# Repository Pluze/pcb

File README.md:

# PCB

Reference and experimental PCB designs built with KiCad, plus reusable agent workflows for schematic capture, placement, routing, and verification.

## Contents

- [`Designs/LM555_LED_Flasher`](Designs/LM555_LED_Flasher): an all-SMT, single-sided 555 timer LED flasher adapted from a classroom reference.
- [`Designs/Ionto_Current_Source_Core`](Designs/Ionto_Current_Source_Core): a single-channel R1218 constant-current boost prototype.
- [`Designs/Electrode_Snap_Adapter_Series`](Designs/Electrode_Snap_Adapter_Series): four circular-contact adapters and a 17-up U4 panel.
- [`tools/pcbflow`](tools/pcbflow): public CLI, reusable engines and tests for humans and agents.
- [`.agents/skills`](.agents/skills): engineering methods and shared design defaults.

## Design Philosophy

Design intent is made explicit before editing. Schematic connectivity, footprints, placement, routing, silkscreen, and final renders are validated as separate gates. Classroom and prototype boards favor readable documentation, common packages, generous geometry, and reproducible evidence.

The workflows draw on KiCad's official IPC model and public agent-oriented KiCad projects, while keeping tool-specific claims tied to verified local behavior. See each design's `VALIDATION.md` for measured results and remaining warnings.

Use `./pcb finish --design NAME` to complete a saved design through clean autorouting,
review, adoption, copper pour and production build. Use `./pcb build` to refresh U4,
LightBurn and complete supplier Gerber packages together. `./pcb verify` checks the
current delivery. Add `--json` before the command for agent-readable results.

The [tool guide](tools/pcbflow/README.md) covers human/agent handoffs, staged commands,
advanced tools, output ownership and verification commands.

## Status

These projects are educational references and experiments. They are not production-certified hardware. Verify component data, electrical limits, PCB fabrication rules, assembly requirements, and safety constraints before manufacturing or use.

## Contributing

Read [`AGENTS.md`](AGENTS.md), [`Designs/AGENTS.md`](Designs/AGENTS.md), and [`CONTRIBUTING.md`](CONTRIBUTING.md) before changing a design.

## License

MIT. See [`LICENSE`](LICENSE).

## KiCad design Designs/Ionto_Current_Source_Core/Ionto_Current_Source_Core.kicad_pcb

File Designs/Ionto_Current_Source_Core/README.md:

# R1218N041A Single-Channel Constant-Current Core

This project is a minimum verifiable implementation of the paper's R1218-based stimulation architecture. It accepts a protected 1-cell LiPo and provides one two-wire constant-current output. Charging, timing, wireless power, channel decoding, switches, and miniaturization are deliberately omitted.

This is an experimental electrical prototype, not a medically certified device. Do not connect it to a person until current limits, isolation, electrodes, open-load behavior, fault behavior, and applicable safety requirements have been reviewed by a qualified engineer.

## Electrical operation

`U1` is `R1218N041A-TR-FE`, a SOT-23-6 boost LED/current driver with an internal switch, internal rectifier diode, 0.2 V feedback reference, and approximately 18.5 V typical over-voltage protection. `CE` is routed to J3 instead of being permanently tied high.

J3 is a two-pin 2.54 mm SMT header:

- Pin 1: VIN / always-on source
- Pin 2: CE / external enable input

Fit a standard 2.54 mm shunt across pins 1–2 for always-on operation. Remove the shunt and drive pin 2 for external control. The external controller must share board GND through a separate ground connection.

The R1218 includes a CE pull-down specified at 600 kΩ to 2.2 MΩ, so removing the shunt leaves the converter disabled even when no external controller is attached. For an external logic source, the datasheet specifies CE low at no more than 0.5 V and CE high at at least 1.5 V; the CE pin must remain within its absolute input limits relative to the battery/GND domain.

The current path is:

`VBAT → L1 → U1 internal boost stage → VOUT → J2 pin 1 → external load → J2 pin 2 → VFB → R1 → GND`

U1 regulates the VFB node to nominally 0.2 V, so:

`ISTIM = 0.2 V / R1`

The default `R1 = 536 Ω ±1%` gives `ISTIM ≈ 373 µA`, corresponding to approximately 0.261 mA/cm² over 143 mm². For the 199 mm² electrode, use the 402 Ω carrier for approximately 498 µA or 0.250 mA/cm². The R1218 feedback specification is 0.19–0.21 V, so IC feedback tolerance alone produces approximately ±5% current variation before resistor tolerance and operating effects.

## Assembly-selected current

| R1 | Nominal current | Use |
|---:|---:|---|
| 665 Ω | 301 µA | Low end of configured range |
| 536 Ω | 373 µA | 143 mm² default |
| 402 Ω | 498 µA | 199 mm² default |
| 267 Ω | 749 µA | Intermediate setting |
| 200 Ω | 1.00 mA | Larger-area validation setting |
| 133 Ω | 1.50 mA | Nominal maximum setting |

For a fixed-current carrier, use one fixed resistor per assembly. The main board carries a two-position 2.54 mm SMT female socket. R1 is mounted on a removable two-pin RSET carrier made from a mating `TSM-102-01-S-SV` header and a tiny carrier PCB; it is not inserted into the socket as a bare 0805 part. This keeps resistor changes solder-free at the core board. Do not populate multiple fixed values in parallel.

For bench adjustment, a Bourns `3223W-1-102E` 1 kΩ, 11-turn, top-adjust SMD trimmer can replace the fixed RSET electrically. Connect it as a two-terminal rheostat by tying the wiper to one end, then connect those two effective terminals to the two existing RSET pads. Its physical three-pad footprint does not match the present two-pad RSET socket, so use short wires or a simple two-pin header connection for validation rather than soldering it directly onto the socket footprint. Approximately 667 Ω sets 300 µA, 402 Ω sets 498 µA, 267 Ω sets 749 µA, 200 Ω sets 1.00 mA, and 133 Ω sets 1.50 mA. Preset the resistance with a meter before power-up; the trimmer scale is not a calibrated current indication.

## Component roles and selected parts

| Ref | Selected part/value | Package/footprint | Purpose |
|---|---|---|---|
| J1 | Samtec `TSM-102-01-S-SV` | 1×2, 2.54 mm vertical SMT header | Protected 1S LiPo input; pin 1 BAT+, pin 2 GND; accepts a simple flying-lead harness |
| U1 | Nisshinbo `R1218N041A-TR-FE` | SOT-23-6 | Boost conversion and 0.2 V constant-current regulation |
| L1 | Bourns `SRN4018-220M`, 22 µH | 4.0 × 4.0 mm SMD | Boost energy storage; 900 mA rated, shielded |
| C1 | Murata `GRM21BR71A105KA01L`, 1 µF 10 V X7R | 0805 hand-solder pads | Battery/input bypass |
| C2 | KEMET `C0805C224K5RACTU`, 0.22 µF 50 V X7R | 0805 hand-solder pads | Boost/output filtering |
| R1 | Yageo `RC0805FR-07536RL`, 536 Ω 1% | 0805 on removable two-pin RSET carrier | Default 373 µA setting for 143 mm² electrode |
| RT1 option | Bourns `3223W-1-102E`, 1 kΩ ±20%, 11-turn | 3.9 × 3.2 mm top-adjust SMD trimmer connected to the two RSET pads | Adjustable validation replacement for the fixed RSET |
| XS1 | Samtec `SSM-102-L-SV-K-TR` | 1×2, 2.54 mm vertical SMT female socket | Board-side receptacle for the removable RSET carrier; represented by R1's footprint in the current schematic |
| XP1 | Samtec `TSM-102-01-S-SV` | 1×2, 2.54 mm vertical SMT male header | Mating connector on the removable RSET carrier |
| J2 | Samtec `TSM-102-01-S-SV` | 1×2, 2.54 mm vertical SMT header | Stimulation output; pin 1 STIM+, pin 2 STIM−/VFB; accepts a simple flying-lead harness |
| J3 | Samtec `TSM-102-01-S-SV` | 1×2, 2.54 mm vertical SMT header | VIN-to-CE always-on jumper and external CE input |

The R1218 contains the boost rectifier diode, so the design intentionally has no external Schottky diode. C1 and C2 meet the datasheet's minimum application values, and L1 is within the recommended 10–22 µH range.

Distributor evidence checked 2026-09-16: DigiKey listed the R1218N041A, SRN4018-220M, C1, C2, the Samtec SSM-102 board socket, and the TSM-102 two-pin SMT header used by the RSET carrier and CE jumper as active and available. The selected Yageo 0805 RSET values covering approximately 300 µA–1.50 mA were checked on 2026-09-17 and selected from active, cut-tape parts with substantial DigiKey stock. The optional Bourns `3223W-1-102E` SMD trimmer was also active and available in cut tape. Inventory is volatile and must be rechecked before ordering.

The English, text-only procurement table is stored in [`BOM.csv`](BOM.csv). It includes the five-board build quantities, RSET options, selected DigiKey order numbers, useful 0805 stock parts, price estimates, and the dated inventory snapshot. Recheck price, stock, lifecycle, and exact order suffix before purchasing.

J1, J2, J3, and the removable RSET carrier deliberately reuse the same 2.54 mm connector family wherever mating gender permits. This minimizes unique inventory and makes future connector changes a harness or small-adapter problem rather than a core-board redesign.

## PCB implementation

The active board is 27 × 20 mm. All eight footprints and all routed copper are on the front side, with zero vias; the production pour variant adds a front-side GND zone while the matching primary remains routing-only. The placement follows the power/current path from the battery header at the left, through the inductor and R1218 stage, to the stimulation header at the right. The CE jumper sits beside the controller/output area, and the removable RSET socket remains accessible along the lower edge.

Freerouting-derived routing uses 0.25 mm (about 10 mil) for control and local GND,
0.30 mm (about 12 mil) for stimulation, and 0.50 mm (about 20 mil) for BAT+, LX and
the outer GND return. The final 53 front-copper segments have only horizontal,
vertical and 45-degree directions. Explicit GND routes connect every component
without relying on the pour. Total trace length is 113.45 mm; LX is 3.00 mm and
remains local to U1/L1. The project offers approximately
6–20 mil presets, with a 0.1524 mm selectable minimum and 0.20 mm clearance;
actual tracks remain at least 0.25 mm.

For the soldermask-free LPKF U4 prototype, the front GND zone uses 0.50 mm clearance to other-net copper and a 0.50 mm edge inset, with 0.25 mm minimum fill thickness, a 0.50 mm thermal gap and 0.50 mm spokes. Actual copper-removal time still depends on the CircuitPro recipe. Explicit GND routes retain connectivity without the pour. C1 and C2 retain deliberate solid-zone pad connections.

The matching primary PCB is intentionally the routing-only design source and contains no zone. It must pass DRC with zero unconnected items before production generation derives [`variants/Ionto_Current_Source_Core_With_Pour.kicad_pcb`](variants/Ionto_Current_Source_Core_With_Pour.kicad_pcb). The production exporter refills and checks a temporary copy of that 0.50 mm GND-zone definition, leaving both design sources unchanged.

The repo-wide [`repository-defaults.json`](../../.agents/skills/kicad-pcb-layout/references/repository-defaults.json) owns the common route-first workflow, single-sided/zero-via policy, 0.20 mm default clearance and 0.25 mm routing width, wider functional net classes, explicit GND-tree requirement, 0.50 mm pour clearance and edge inset, thermal settings, DRC gates, and automatic dual manufacturing outputs. KiCad project classes use those functional targets. Local GND uses the ordinary class; the established outer return is explicitly 0.50 mm.

CircuitPro-ready single-sided U4 Gerber output is under [`fabrication/u4/Ionto_Current_Source_Core/`](fabrication/u4/Ionto_Current_Source_Core/) for the routing-only primary and [`fabrication/u4/Ionto_Current_Source_Core_With_Pour/`](fabrication/u4/Ionto_Current_Source_Core_With_Pour/) for the generated pour variant. Each package contains only `TopLayer.gtl` and `BoardOutline.gm1` because the PCB has no back copper, vias, or drilled holes.

Matching LightBurn templates are under [`fabrication/lightburn/Ionto_Current_Source_Core/`](fabrication/lightburn/Ionto_Current_Source_Core/) and [`fabrication/lightburn/Ionto_Current_Source_Core_With_Pour/`](fabrication/lightburn/Ionto_Current_Source_Core_With_Pour/). Each `FrontMask_TopView.dxf` is a millimetre vector export of `F.Mask` plus `Edge.Cuts`; laser settings are intentionally not stored in the geometry file.

## Schematic contract and archive

`schematic_topology.json` is the pin-level connectivity contract. The reviewed KiCad sheet is the presentation source of truth. Ordinary topology is shown by explicit orthogonal wires; only the conventional common GND network uses repeated power symbols.

## Known engineering limitation

The fixed and adjustable RSET values provide nominal settings from approximately 300 µA to 1.50 mA. The R1218 datasheet specifies a 400 mA internal switch, a 400–1000 mA switch-current-limit range, and application examples up to 20 mA load current, so 1.50 mA is well below the converter's demonstrated load-current range. Actual regulated current still follows feedback-voltage tolerance and must be measured across battery voltage and representative load resistance. A truly open output draws no regulated load current and tests OVP behavior only; use a suitable dummy load to verify current regulation.

## Trace sizing

The 0.50 mm BAT/switching trunk is evaluated for this low-output-current prototype,
not adopted as a universal current rating. Using bulk copper resistivity of about
0.0172 ohm mm²/m, a 10 mm long, 0.50 mm wide, 18 µm thick straight trace is about
19 mΩ. At a conservative 1 A pulse reference it drops about 19 mV and dissipates
about 19 mW; actual average loss depends on RMS current. BAT+ and LX routes remain 0.50 mm throughout. These estimates do not establish temperature rise, copper thickness
or fault-current qualification. Confirm real copper/process quality and loaded
behavior on the bench. Wider traces remain appropriate when a new design needs them.

## Supplier Gerbers and unified build

`./pcb build --design Ionto_Current_Source_Core` refreshes U4, LightBurn DXF and
[`fabrication/gerber/`](fabrication/gerber/) together. Each supplier package includes
all declared layers, the native Gerber job, PTH/NPTH drill files and `PACKAGE.md`
with layer mapping and order parameters to confirm. For the complete saved-design
routing workflow, use the repository [tool guide](../../tools/pcbflow/README.md).

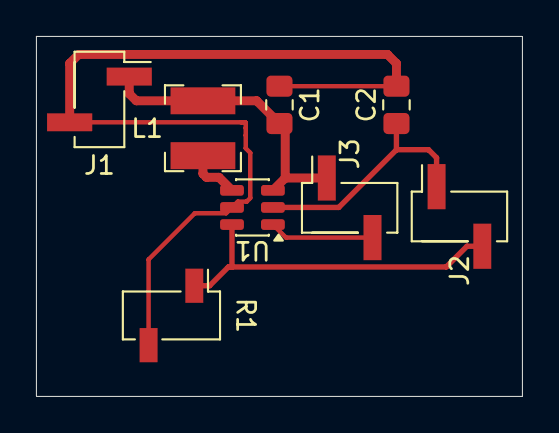
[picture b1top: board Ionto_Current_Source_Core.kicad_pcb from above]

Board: 2 copper layers, 27.0 x 20.0 mm, 8 parts (0 on the bottom side), 6 nets.

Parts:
C1: 1uF 10V X7R; C_0805_2012Metric_Pad1.18x1.45mm_HandSolder
C2: 220nF 50V X7R; C_0805_2012Metric_Pad1.18x1.45mm_HandSolder
J1: BATTERY INPUT 3.0-4.2V; PinHeader_1x02_P2.54mm_Vertical_SMD_Pin1Right
J2: STIM OUTPUT; PinHeader_1x02_P2.54mm_Vertical_SMD_Pin1Right
J3: CE JUMPER: 1=VIN 2=CE; PinHeader_1x02_P2.54mm_Vertical_SMD_Pin1Right
L1: 22uH; L_Bourns-SRN4018
R1: RSET MODULE 536R (373uA); PinSocket_1x02_P2.54mm_Vertical_SMD_Pin1Left
U1: R1218N041A-TR-FE; SOT-23-6

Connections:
GND: C1.2, C2.2, J1.2, R1.2, U1.5
unnamed: C1.1, J1.1, J3.1, L1.1, U1.3
unnamed: C2.1, J2.1, U1.2
unnamed: J2.2, R1.1, U1.6
unnamed: J3.2, U1.1
unnamed: L1.2, U1.4

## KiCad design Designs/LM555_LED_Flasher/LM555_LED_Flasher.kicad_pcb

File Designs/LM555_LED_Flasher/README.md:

# LM555 LED Flasher

An educational astable 555 timer that flashes one LED. The design adapts the classroom topology into a compact, readable, all-SMT KiCad project intended for simple prototype fabrication.

## Circuit

- `U1`: LM555xM, SOIC-8.
- `R1`: 1 kΩ, 0603.
- `R2`: 100 kΩ, 0603.
- `R3`: 330 Ω LED current limiter, 0603.
- `C1`: 10 µF polarized SMD aluminum electrolytic, 5 × 5.3 mm.
- `C2`: 10 nF, 0603, control-voltage bypass.
- `D1`: generic indicator LED, 0805.
- `BT1`: 2-pin JST-PH SMD power connector.

The timing network follows the standard astable relationship approximately described by `f = 1.44 / ((R1 + 2R2) × C1)`. Actual flash rate depends on component tolerance, leakage, and the chosen 555 variant.

## Component Strategy

All board-mounted parts are SMT. The 0805 LED remains visible and hand-solderable; the 0603 passives keep the board compact without forcing unusually small geometry.

`C1` does not electrically have to be electrolytic. This implementation uses an SMD aluminum electrolytic because its effective 10 µF capacitance is more predictable across a typical low-voltage supply than a small high-value MLCC subject to DC-bias derating. A ceramic alternative should use an adequately rated 1206 or 1210 X7R part, verify effective capacitance at the actual bias voltage, and recalculate the timing range.

`D1` is intentionally generic because the classroom reference does not specify color or optical output. Select a real 0805 LED whose forward voltage and current are compatible with the supply, LM555 output capability, and `R3`; re-evaluate `R3` if those assumptions change.

## Layout Intent

- Board outline: approximately 40 mm × 25 mm with rounded corners.
- Components and all routing are on `F.Cu`.
- Zero vias and zero jumper resistors are used.
- Freerouting-derived tracks are 0.25 mm, with 45-degree bends and zero degree-two right-angle corners.
- The connector is placed at the left edge, the LED/output section follows it, the timer occupies the center, and timing components sit to the right.
- Designators and polarity marks are kept upright, visible, and inside the board.

## Reference Adaptation

The schematic preserves the classroom circuit's recognizable power rails, 555 pin relationships, timing divider, control bypass, and LED output path. Layout geometry was adjusted where KiCad symbol geometry, SMT packages, electrical loop length, or silkscreen readability required it.

## Manufacturing Outputs

[`fabrication/u4/LM555_LED_Flasher/`](fabrication/u4/LM555_LED_Flasher/) contains the PCB-derived CircuitPro package. [`fabrication/lightburn/LM555_LED_Flasher/`](fabrication/lightburn/LM555_LED_Flasher/) contains the PCB-derived front solder-mask DXF. The shared exporter infers the used copper side, mask side, and absence of drill data directly from the KiCad PCB.

The project routing menu now includes approximately 6–20 mil sizes, with a 0.25 mm
default, a selectable 0.1524 mm minimum and 0.20 mm clearance. The optimized 62-segment routing totals 123.26 mm. The generated [`variants/LM555_LED_Flasher_With_Pour.kicad_pcb`](variants/LM555_LED_Flasher_With_Pour.kicad_pcb)
uses the repository's 0.50 mm GND pour clearance and edge inset. Corresponding
`LM555_LED_Flasher_With_Pour` directories under all three fabrication formats contain the
second production option. The primary board remains the routing-only source.

## Limitations

This is a reference and experimental design, not a production release. Confirm the exact LM555 variant, supply range, LED, capacitor voltage rating, connector polarity, fabrication rules, and assembly process before building it.

U1 pin 1 uses explicit GND routing with no direct zone connection (`zone_connect 0`).
The 0.50 mm pour moat otherwise allowed only one thermal spoke at that pad; this
local assembly choice removes the starved thermal without relaxing the DRC rule.
Pad geometry and net assignment are unchanged.

## Supplier Gerbers and unified build

`./pcb build --design LM555_LED_Flasher` refreshes U4, LightBurn DXF and
[`fabrication/gerber/`](fabrication/gerber/) together. Each supplier package includes
all declared layers, the native Gerber job, PTH/NPTH drill files and `PACKAGE.md`
with layer mapping and order parameters to confirm. For the complete saved-design
routing workflow, use the repository [tool guide](../../tools/pcbflow/README.md).

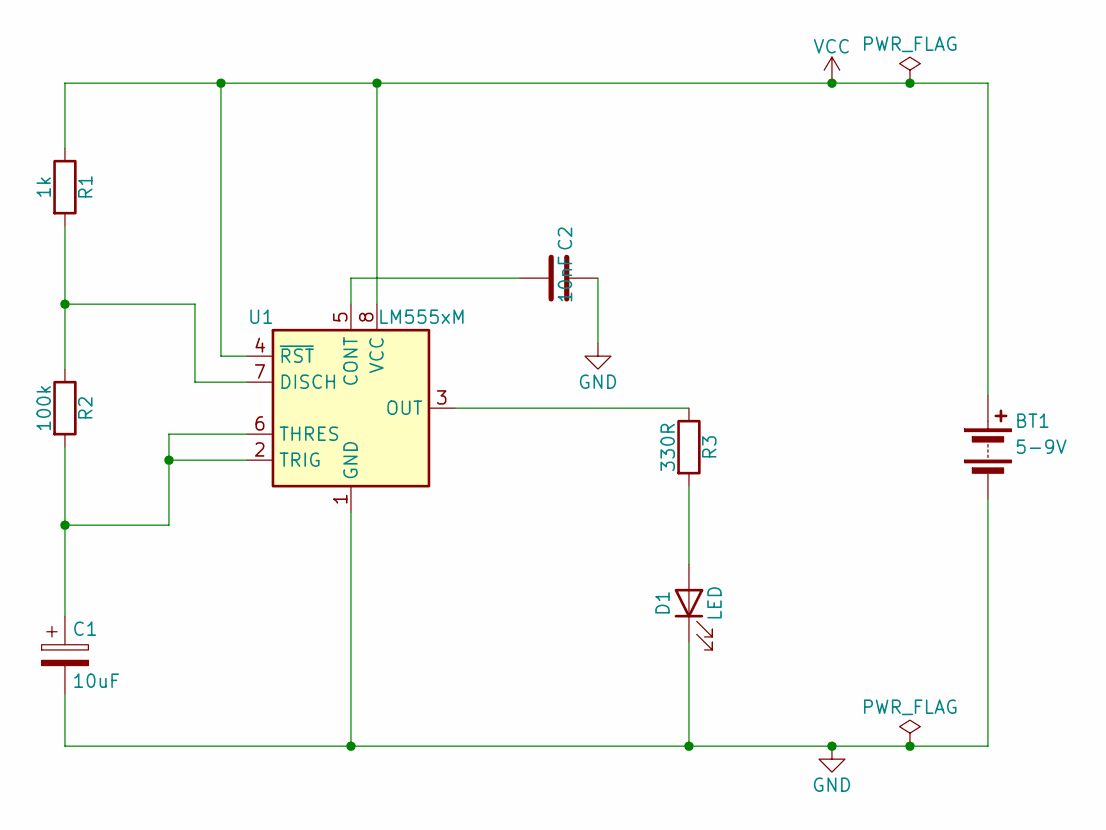
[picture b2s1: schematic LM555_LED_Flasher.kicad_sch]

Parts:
BT1: 5-9V; JST_PH_B2B-PH-SM4-TB_1x02-1MP_P2.00mm_Vertical
C1: 10uF; CP_Elec_5x5.3
C2: 10nF; C_0603_1608Metric
D1: LED; LED_0805_2012Metric
R1: 1k; R_0603_1608Metric
R2: 100k; R_0603_1608Metric
R3: 330R; R_0603_1608Metric
U1: LM555xM; SOIC-8_3.9x4.9mm_P1.27mm

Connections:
GND: BT1.2 (-), C1.2, C2.2, D1.1 (K), U1.1 (GND)
unnamed: D1.2 (A), R3.2
unnamed: C2.1, U1.5 (CONT)
unnamed: R1.2, R2.1, U1.7 (DISCH)
unnamed: R3.1, U1.3 (OUT)
unnamed: C1.1, R2.2, U1.2 (TRIG), U1.6 (THRES)
VCC: BT1.1 (+), R1.1, U1.4 (~RST), U1.8 (VCC)

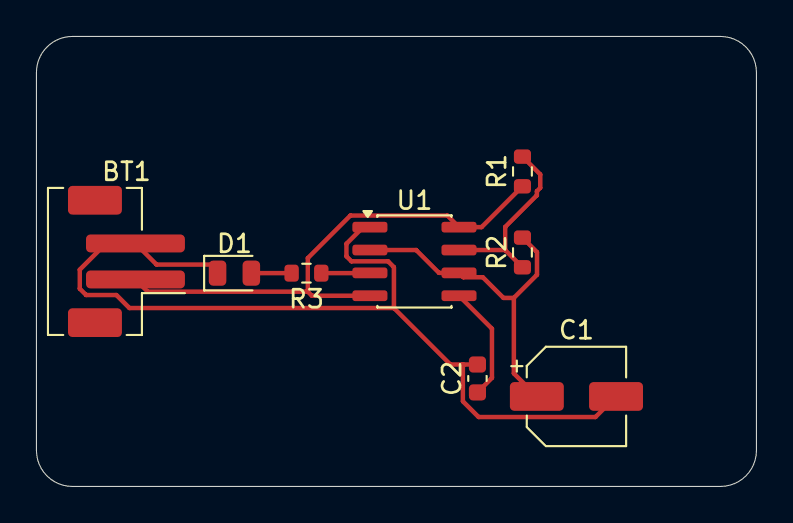
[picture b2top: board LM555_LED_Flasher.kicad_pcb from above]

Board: 2 copper layers, 40.0 x 25.0 mm, 8 parts (0 on the bottom side), 7 nets.
